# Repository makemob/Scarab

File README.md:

# Scarab
H-Bridge motor/actuator controller with RS-485 comms

- Based around NXP LPC1114 Microcontroller
- 13-48VDC input (36V nominal)
- 8A average current output
- 12VDC max 200mA auxiliary output
- 3.3VDC auxiliary output ~40mA at 25 deg C, <10mA at 85 deg C
- Good to 85 deg C ambient (in theory)
- RS-485 comms, aux analog and digital I/O
- 3 x indicator LEDs
- NTC temperature sensor
- Battery voltage sensing

All specifications are indicative..

Designed to drive Linak LA-35 linear actuators for the MakeMob UKI - Utility Kinetic Insect project http://makemob.net/portfolio_page/uki-electric-insect-vehicle/

Suitable for all kinds of other clever tricks

Firmware available at http://github.com/makemob/huhu

Licensed under Creative Commons Attribution Share Alike 4.0, https://creativecommons.org/licenses/by-sa/4.0/legalcode.txt

BOM adjustments since v1.0:
- Replace R1, R2, R8, R9 with 100ohm
- Populate D7 (3V zener), C14 (10nF), D15 & D16 (5V TVS), C25 & C26 (100nF)
- RC snubber across motor output may be required to protect gate drivers from overvoltage (it is if you want to run LA-35 actuators at 36V..)

Next time:
- Locating C1 closer to the bridge may improve transients
- BAV99 footprints are wrong, need to jam them on sideways (D6, D7, D19)

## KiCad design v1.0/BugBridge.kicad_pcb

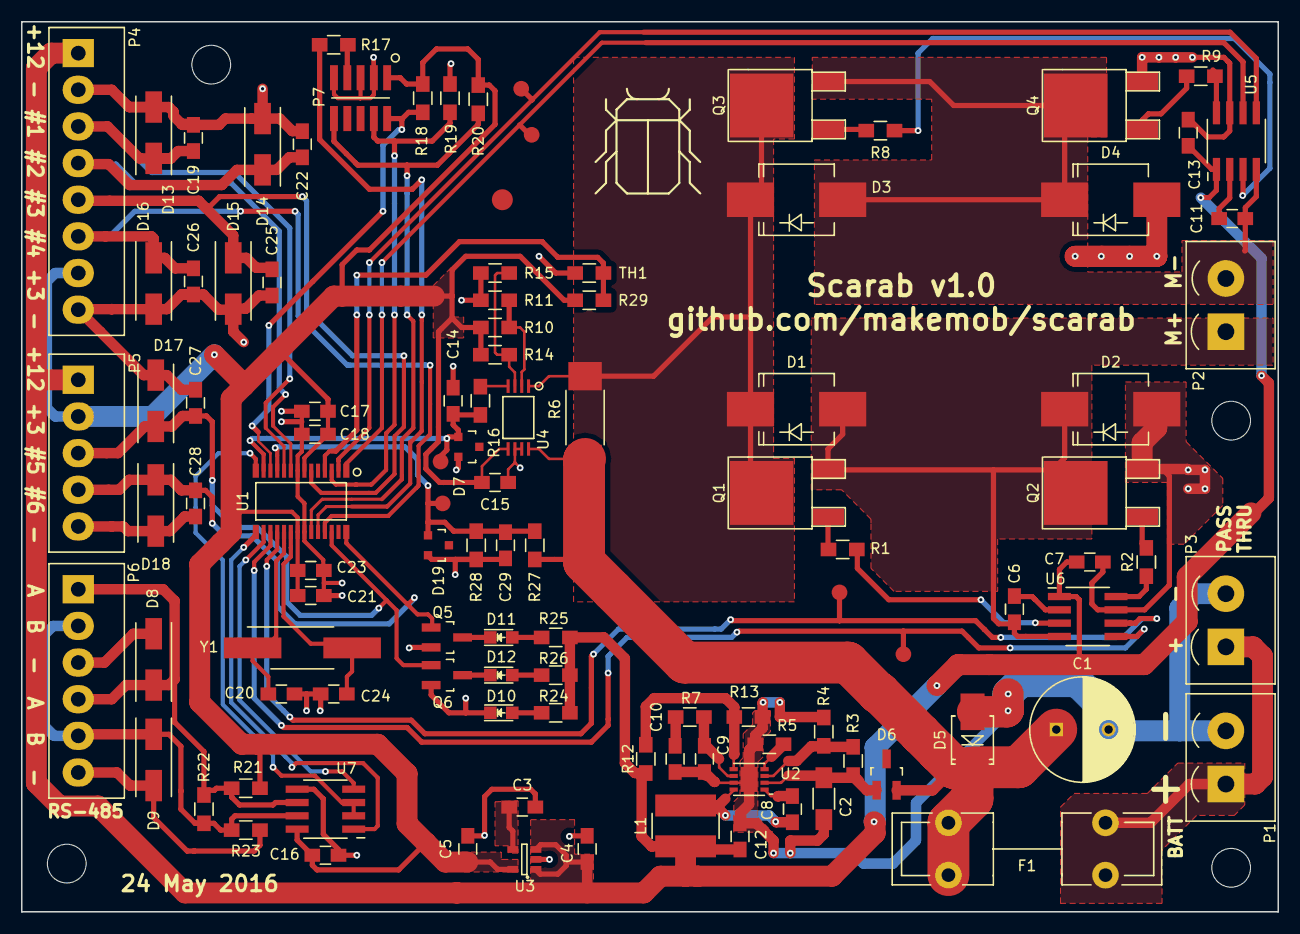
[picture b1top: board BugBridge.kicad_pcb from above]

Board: 2 copper layers, 120.0 x 85.0 mm, 101 parts (0 on the bottom side), 60 nets.

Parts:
C1: 150uF; C_Radial_D10_L20_P5
C2: 2.2uF; C_1206_HandSoldering
C3, C14, C19, C22, C25, C26, C27, C28: NF; C_0805_HandSoldering
C4, C5: 1uF; C_0805_HandSoldering
C6, C7, C11, C13: 1uF 25V X7R; C_0805_HandSoldering
C8, C18, C23, C29: 10nF; C_0805_HandSoldering
C9: 68pF; C_0805_HandSoldering
C10: 750pF; C_0805_HandSoldering
C12: 10uF; C_0805_HandSoldering
C15, C16, C17, C21: 100nF; C_0805_HandSoldering
C20, C24: 39pF; C_0805_HandSoldering
D1, D2, D3, D4: NF; SMC_Handsoldering
D5: TVS; SMB_Handsoldering
D6: BAV99; SOT-23_Handsoldering
D7: NF; SOT-23
D8, D9: TVS 12V; DO-214AC_Handsoldering
D10: RED; LED_0805
D11: BLUE; LED_0805
D12: GREEN; LED_0805
D13, D14, D15, D16, D17, D18: NF; DO-214AC_Handsoldering
D19: 3V; SOT-23
F1: 8A; Fuseholder_5x20_Schurter
L1: 220uH 1.57R; INDUCTOR_SDR0604
P1: BATT; Connector_5.08mm_Pitch_2way
P2: MOTOR; Connector_5.08mm_Pitch_2way
P3: PASSTHRU; Connector_5.08mm_Pitch_2way
P4: AUX_A; Connector_3.5mm_Pitch_8way
P5: AUX_B; Connector_3.5mm_Pitch_5way
P6: COMMS; Connector_3.5mm_Pitch_6way
P7: ISP; CON_02X05_1.27
Q1, Q2, Q3, Q4: IPD35N10S3L-26; TO-252-2Lead
Q5, Q6: MMUN2211LT1G; SOT-23_Handsoldering
R1, R2, R8, R9, R11, R15, R17: 0R; R_0805_HandSoldering
R3, R4, R10, R14, R20, R21, R22, R23: NF; R_0805_HandSoldering
R5: 97.6k; R_0805_HandSoldering
R6: 0.01R 1W; R_2512_HandSoldering
R7: 158k; R_0805_HandSoldering
R12: 140k; R_0805_HandSoldering
R13, R28, R29: 10k; R_0805_HandSoldering
R16: 1k; R_0805_HandSoldering
R18, R19: 47k; R_0805_HandSoldering
R24, R25, R26: 1k8; R_0805_HandSoldering
R27: 120k; R_0805_HandSoldering
TH1: NTCS0805E3103JMT; R_0805_HandSoldering
U1: LPC1114FDH28/102; TSSOP-28
U2: TPS54061; VSON8
U3: MIC5205-3.3YM5; SOT-23-5
U4: ST_CS70; TSSOP8
U5, U6: MIC4605-1YM; SOIC-8_Pitch1.27mm
U7: MAX3485; SOIC-8_Pitch1.27mm
Y1: 12MHz 20pF; Crystal_FOX_HC

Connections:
+3V3: C5.1, C15.2, C16.1, C17.1, C18.1, C21.1, C23.1, P4.7, P5.2, P7.1, R10.1, R14.1, R18.1, R20.1, R21.1, R29.1, U1.7, U1.21, U3.5, U4.5, U7.8
+12V: C4.1, C7.1, C12.1, C13.2, L1.2, P4.1, P5.1, R12.1, R24.1, R25.1, R26.1, U3.1, U3.3, U5.1, U6.1
+BATT: C1.1, D5.1, D6.2, F1.2, R6.1, R27.1, U4.8
/BugBridge Micro/485_TX_EN: U1.14, U7.2, U7.3
/BugBridge Micro/BATT_V_SENSE: C29.1, D19.1, R27.2, R28.1, U1.11
/BugBridge Micro/BRIDGE_1: U1.17, U6.5
/BugBridge Micro/BRIDGE_2: U1.18, U6.6
/BugBridge Micro/BRIDGE_3: U1.2, U5.5
/BugBridge Micro/BRIDGE_4: U1.1, U5.6
/BugBridge Micro/EXT_1: C19.1, D13.1, P4.3, U1.10
/BugBridge Micro/EXT_2: C22.1, D14.1, P4.4, U1.9
/BugBridge Micro/EXT_3: C25.1, D15.1, P4.5, U1.6
/BugBridge Micro/EXT_4: C26.1, D16.1, P4.6, U1.25
/BugBridge Micro/EXT_5: C27.1, D17.1, P5.3, Q6.1, U1.26
/BugBridge Micro/EXT_6: C28.1, D18.1, P5.4, Q5.1, U1.28
/BugBridge Micro/I_SENSE: C14.1, D7.1, R16.1, U1.13
/BugBridge Micro/PG_CLK: P7.4, R19.1, U1.3
/BugBridge Micro/PG_DATA: P7.2, R18.2, U1.12
/BugBridge Micro/PG_ISP: R17.2, U1.24
/BugBridge Micro/PG_RESET: P7.10, R20.2, U1.23
/BugBridge Micro/RS-485_A: D8.1, P6.1, P6.4, R21.2, R22.1, U7.6
/BugBridge Micro/RS-485_B: D9.1, P6.2, P6.5, R22.2, R23.1, U7.7
/BugBridge Micro/TEMP: R29.2, TH1.1, U1.4
/BugBridge Micro/UART_RX: U1.15, U7.1
/BugBridge Micro/UART_TX: U1.16, U7.4
/BugBridge Power/BATT+: F1.1, P1.1, P3.1
/BugBridge Power/MOTOR_A: C6.1, D1.2, D2.1, P2.1, Q1.3, Q2.2, U6.4
/BugBridge Power/MOTOR_B: C11.2, D3.2, D4.1, P2.2, Q3.3, Q4.2, U5.4
GND: C1.2, C2.2, C3.2, C4.2, C5.2, C7.2, C9.2, C10.2, C12.2, C13.1, C14.2, C15.1, C16.2, C17.2, C18.2, C19.2, C20.2, C21.2, C22.2, C23.2, C24.2, C25.2, C26.2, C27.2, C28.2, C29.2, D2.2, D4.2, D5.2, D7.2, D8.2, D9.2, D10.1, D13.2, D14.2, D15.2, D16.2, D17.2, D18.2, D19.2, P1.2, P3.2, P4.2, P4.8, P5.5, P6.3, P6.6, P7.3, P7.5, P7.9, Q2.3, Q4.3, Q5.2, Q6.2, R4.2, R5.2, R11.2, R13.2, R15.2, R19.2, R23.2, R28.2, TH1.2, U1.8, U1.22, U2.7, U2.9, U3.2, U4.6, U4.7, U5.7, U6.7, U7.5
unnamed: C2.1, D6.1, R3.1, U2.2
unnamed: C3.1, U3.4
unnamed: C6.2, U6.2
unnamed: C8.1, L1.1, U2.8
unnamed: C8.2, U2.1
unnamed: C9.1, R7.2, U2.6
unnamed: C10.1, R7.1
unnamed: C11.1, U5.2
unnamed: C20.1, U1.19, Y1.1
unnamed: C24.1, U1.20, Y1.2
unnamed: D1.1, D3.1, Q1.2, Q3.2, R6.2, U4.1
unnamed: D10.2, R24.2
unnamed: D11.1, Q5.3
unnamed: D11.2, R25.2
unnamed: D12.1, Q6.3
unnamed: D12.2, R26.2
unnamed: P7.7, R17.1
unnamed: Q1.1, R1.1
unnamed: Q2.1, R2.1
unnamed: Q3.1, R8.2
unnamed: Q4.1, R9.2
unnamed: R1.2, U6.3
unnamed: R2.2, U6.8
unnamed: R3.2, R4.1, U2.3
unnamed: R5.1, U2.4
unnamed: R8.1, U5.3
unnamed: R9.1, U5.8
unnamed: R10.2, R11.1, U4.2
unnamed: R12.2, R13.1, U2.5
unnamed: R14.2, R15.1, U4.3
unnamed: R16.2, U4.4

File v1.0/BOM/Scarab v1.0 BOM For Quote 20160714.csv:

Reference, Value, Footprint, Datasheet
P1,BATT,BugBridgePCBLib:Connector_5.08mm_Pitch_2way,
P2,MOTOR,BugBridgePCBLib:Connector_5.08mm_Pitch_2way,
P4,AUX_A,BugBridgePCBLib:Connector_3.5mm_Pitch_8way,
P6,COMMS,BugBridgePCBLib:Connector_3.5mm_Pitch_6way,
P3,PASSTHRU,BugBridgePCBLib:Connector_5.08mm_Pitch_2way,
P5,AUX_B,BugBridgePCBLib:Connector_3.5mm_Pitch_5way,
C8,10nF,Capacitors_SMD:C_0805_HandSoldering,
C2,2.2uF,Capacitors_SMD:C_1206_HandSoldering,
C9,68pF,Capacitors_SMD:C_0805_HandSoldering,
R3,NF,Resistors_SMD:R_0805_HandSoldering,
R4,NF,Resistors_SMD:R_0805_HandSoldering,
R12,140k,Resistors_SMD:R_0805_HandSoldering,
R13,10k,Resistors_SMD:R_0805_HandSoldering,
L1,220uH 1.57R,BugBridgePCBLib:INDUCTOR_SDR0604,
C12,10uF,Capacitors_SMD:C_0805_HandSoldering,
U2,TPS54061,BugBridgePCBLib:VSON8,
R7,158k,Resistors_SMD:R_0805_HandSoldering,
C10,750pF,Capacitors_SMD:C_0805_HandSoldering,
R5,97.6k,Resistors_SMD:R_0805_HandSoldering,
F1,8A,BugBridgePCBLib:Fuseholder_5x20_Schurter,
U3,MIC5205-3.3YM5,TO_SOT_Packages_SMD:SOT-23-5,
C4,1uF,Capacitors_SMD:C_0805_HandSoldering,
C3,NF,Capacitors_SMD:C_0805_HandSoldering,
C5,1uF,Capacitors_SMD:C_0805_HandSoldering,
Q1,IPD35N10S3L-26,TO_SOT_Packages_SMD:TO-252-2Lead,
Q2,IPD35N10S3L-26,TO_SOT_Packages_SMD:TO-252-2Lead,
Q3,IPD35N10S3L-26,TO_SOT_Packages_SMD:TO-252-2Lead,
Q4,IPD35N10S3L-26,TO_SOT_Packages_SMD:TO-252-2Lead,
R6,0.01R 1W,Resistors_SMD:R_2512_HandSoldering,
R8,0R,Resistors_SMD:R_0805_HandSoldering,
R9,0R,Resistors_SMD:R_0805_HandSoldering,
R1,0R,Resistors_SMD:R_0805_HandSoldering,
R2,0R,Resistors_SMD:R_0805_HandSoldering,
D1,NF,Diodes_SMD:SMC_Handsoldering,
D3,NF,Diodes_SMD:SMC_Handsoldering,
D4,NF,Diodes_SMD:SMC_Handsoldering,
D2,NF,Diodes_SMD:SMC_Handsoldering,
U4,ST_CS70,BugBridgePCBLib:TSSOP8,
C15,100nF,Capacitors_SMD:C_0805_HandSoldering,
R10,NF,Resistors_SMD:R_0805_HandSoldering,
R11,0R,Resistors_SMD:R_0805_HandSoldering,
R14,NF,Resistors_SMD:R_0805_HandSoldering,
R15,0R,Resistors_SMD:R_0805_HandSoldering,
R16,1k,Resistors_SMD:R_0805_HandSoldering,
C14,NF,Capacitors_SMD:C_0805_HandSoldering,
D7,NF,TO_SOT_Packages_SMD:SOT-23,
U5,MIC4605-1YM,BugBridgePCBLib:SOIC-8_Pitch1.27mm,
U6,MIC4605-1YM,BugBridgePCBLib:SOIC-8_Pitch1.27mm,
C11,1uF 25V X7R,Capacitors_SMD:C_0805_HandSoldering,
C6,1uF 25V X7R,Capacitors_SMD:C_0805_HandSoldering,
C13,1uF 25V X7R,Capacitors_SMD:C_0805_HandSoldering,
C7,1uF 25V X7R,Capacitors_SMD:C_0805_HandSoldering,
D6,BAV99,TO_SOT_Packages_SMD:SOT-23_Handsoldering,
C1,150uF,Capacitors_ThroughHole:C_Radial_D10_L20_P5,
D5,TVS,Diodes_SMD:SMB_Handsoldering,
Y1,12MHz 20pF,BugBridgePCBLib:Crystal_FOX_HC,
C20,39pF,Capacitors_SMD:C_0805_HandSoldering,
C24,39pF,Capacitors_SMD:C_0805_HandSoldering,
C21,100nF,Capacitors_SMD:C_0805_HandSoldering,
C23,10nF,Capacitors_SMD:C_0805_HandSoldering,
C17,100nF,Capacitors_SMD:C_0805_HandSoldering,
C18,10nF,Capacitors_SMD:C_0805_HandSoldering,
P7,ISP,BugBridgePCBLib:CON_02X05_1.27,
R18,47k,Resistors_SMD:R_0805_HandSoldering,
R19,47k,Resistors_SMD:R_0805_HandSoldering,
R20,NF,Resistors_SMD:R_0805_HandSoldering,
U7,MAX3485,BugBridgePCBLib:SOIC-8_Pitch1.27mm,
C16,100nF,Capacitors_SMD:C_0805_HandSoldering,
R21,NF,Resistors_SMD:R_0805_HandSoldering,
R22,NF,Resistors_SMD:R_0805_HandSoldering,
R23,NF,Resistors_SMD:R_0805_HandSoldering,
D8,TVS 12V,BugBridgePCBLib:DO-214AC_Handsoldering,
D9,TVS 12V,BugBridgePCBLib:DO-214AC_Handsoldering,
U1,LPC1114FDH28/102,BugBridgePCBLib:TSSOP-28,
R17,0R,Resistors_SMD:R_0805_HandSoldering,
TH1,NTCS0805E3103JMT,Resistors_SMD:R_0805_HandSoldering,
R29,10k,Resistors_SMD:R_0805_HandSoldering,
R27,120k,Resistors_SMD:R_0805_HandSoldering,
R28,10k,Resistors_SMD:R_0805_HandSoldering,
C29,10nF,Capacitors_SMD:C_0805_HandSoldering,
D19,3V,TO_SOT_Packages_SMD:SOT-23,
D12,GREEN,LEDs:LED_0805,
D10,RED,LEDs:LED_0805,
D11,BLUE,LEDs:LED_0805,
R24,1k8,Resistors_SMD:R_0805_HandSoldering,
R25,1k8,Resistors_SMD:R_0805_HandSoldering,
R26,1k8,Resistors_SMD:R_0805_HandSoldering,
Q5,MMUN2211LT1G,TO_SOT_Packages_SMD:SOT-23_Handsoldering,
Q6,MMUN2211LT1G,TO_SOT_Packages_SMD:SOT-23_Handsoldering,
D13,NF,BugBridgePCBLib:DO-214AC_Handsoldering,
D14,NF,BugBridgePCBLib:DO-214AC_Handsoldering,
D15,NF,BugBridgePCBLib:DO-214AC_Handsoldering,
D16,NF,BugBridgePCBLib:DO-214AC_Handsoldering,
D17,NF,BugBridgePCBLib:DO-214AC_Handsoldering,
D18,NF,BugBridgePCBLib:DO-214AC_Handsoldering,
C19,NF,Capacitors_SMD:C_0805_HandSoldering,
C22,NF,Capacitors_SMD:C_0805_HandSoldering,
C25,NF,Capacitors_SMD:C_0805_HandSoldering,
C26,NF,Capacitors_SMD:C_0805_HandSoldering,
C27,NF,Capacitors_SMD:C_0805_HandSoldering,
C28,NF,Capacitors_SMD:C_0805_HandSoldering,

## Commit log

2016-07-14 v1.0 BOM for quote
2016-07-26 BOM with pricing
2016-08-08 BOM for quote 20160806
2016-08-16 BOM for quote 20160817
2018-12-29 Update encoder wiring diagram
